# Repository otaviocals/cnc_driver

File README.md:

# Arduino Based CNC Driver
## Written by Otavio Cals

# Overview

# Installation

# Credits

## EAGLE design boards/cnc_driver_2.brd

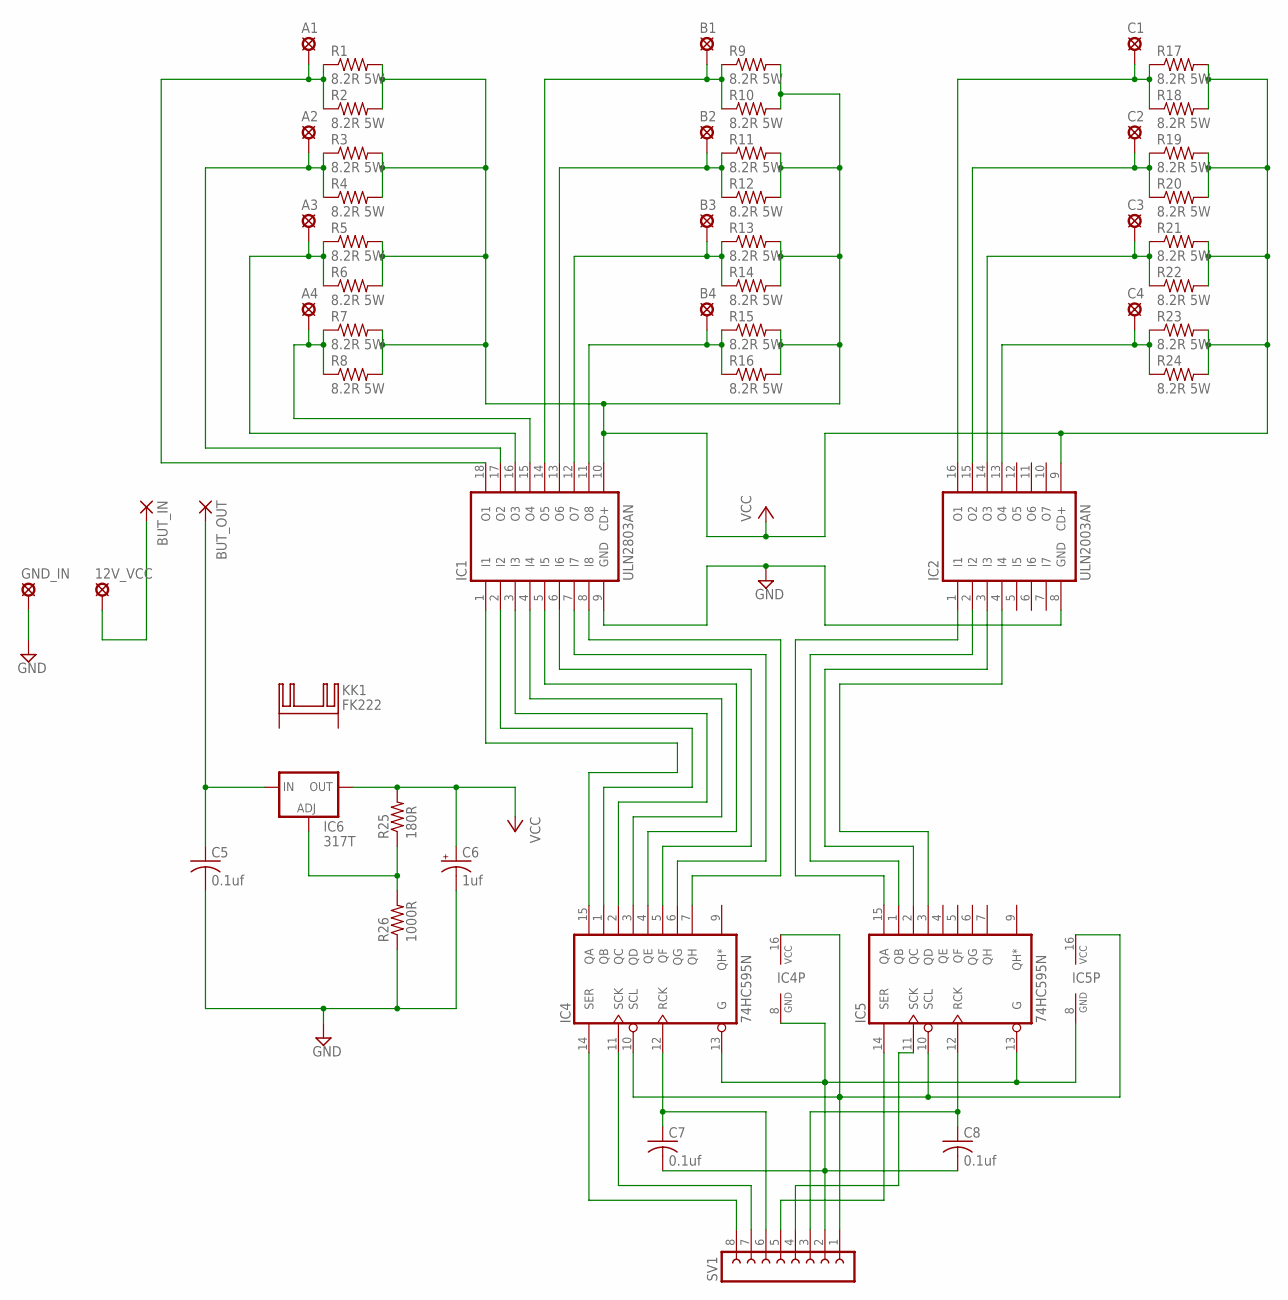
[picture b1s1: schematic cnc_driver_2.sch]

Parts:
12V_VCC: LSP13
A1, A2, A3, A4: LSP11
B1, B2, B3, B4: LSP11
BUT_IN: 3,81/1,4
BUT_OUT: 3,81/1,4
C1, C2, C3, C4: LSP11
C5, C7, C8: 0.1uf; C025-025X050
C6: 1uf; E2-5
GND_IN: LSP13
IC1: ULN2803AN; DIL18
IC2: ULN2003AN; DIL16
IC4, IC5: 74HC595N; DIL16
IC6: 317T; 317TS
KK1: FK222
R1, R2, R3, R4, R5, R6, R7, R8, R9, R10, R11, R12, R13, R14, R15, R16, R17, R18, R19, R20, R21, R22, R23, R24: 8.2R 5W; 0617V
R25: 180R; 0207/10
R26: 1000R; 0207/10
SV1: FE08-1; FE08

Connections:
GND: C5.2, C6.-, GND_IN.MP, IC1.9 (GND), IC2.8 (GND), R26.1
unnamed: A1.MP, IC1.18 (O1), R1.1, R2.1
unnamed: A2.MP, IC1.17 (O2), R3.1, R4.1
unnamed: A3.MP, IC1.16 (O3), R5.1, R6.1
unnamed: A4.MP, IC1.15 (O4), R7.1, R8.1
unnamed: 12V_VCC.MP, BUT_IN.1
unnamed: BUT_OUT.1, C5.1, IC6.3 (IN)
unnamed: IC4.10 (SCL), IC4.16 (VCC), IC5.10 (SCL), IC5.16 (VCC), SV1.1
unnamed: IC6.1 (ADJ), R25.1, R26.2
unnamed: C7.2, C8.2, IC4.8 (GND), IC4.13 (G), IC5.8 (GND), IC5.13 (G), SV1.2
unnamed: B1.MP, IC1.14 (O5), R9.1, R10.1
unnamed: B2.MP, IC1.13 (O6), R11.1, R12.1
unnamed: B3.MP, IC1.12 (O7), R13.1, R14.1
unnamed: B4.MP, IC1.11 (O8), R15.1, R16.1
unnamed: C1.MP, IC2.16 (O1), R17.1, R18.1
unnamed: C2.MP, IC2.15 (O2), R19.1, R20.1
unnamed: C3.MP, IC2.14 (O3), R21.1, R22.1
unnamed: C4.MP, IC2.13 (O4), R23.1, R24.1
unnamed: C8.1, IC5.12 (RCK), SV1.3
unnamed: C7.1, IC4.12 (RCK), SV1.6
unnamed: IC4.11 (SCK), SV1.7
unnamed: IC4.14 (SER), SV1.8
unnamed: IC1.1 (I1), IC4.15 (QA)
unnamed: IC1.2 (I2), IC4.1 (QB)
unnamed: IC1.3 (I3), IC4.2 (QC)
unnamed: IC1.4 (I4), IC4.3 (QD)
unnamed: IC1.5 (I5), IC4.4 (QE)
unnamed: IC1.6 (I6), IC4.5 (QF)
unnamed: IC1.7 (I7), IC4.6 (QG)
unnamed: IC1.8 (I8), IC4.7 (QH)
unnamed: IC2.1 (I1), IC5.15 (QA)
unnamed: IC2.2 (I2), IC5.1 (QB)
unnamed: IC2.3 (I3), IC5.2 (QC)
unnamed: IC2.4 (I4), IC5.3 (QD)
unnamed: IC5.14 (SER), SV1.5
unnamed: IC5.11 (SCK), SV1.4
VCC: IC1.10 (CD+), IC2.9 (CD+), R1.2, R2.2, R3.2, R4.2, R5.2, R6.2, R7.2, R8.2, R9.2, R10.2, R11.2, R12.2, R13.2, R14.2, R15.2, R16.2, R17.2, R18.2, R19.2, R20.2, R21.2, R22.2, R23.2, R24.2
VCC_MOTOR: C6.+, IC6.2 (OUT), R25.2

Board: 2 copper layers, 53 parts (0 on the bottom side), 38 nets, no tracks yet.

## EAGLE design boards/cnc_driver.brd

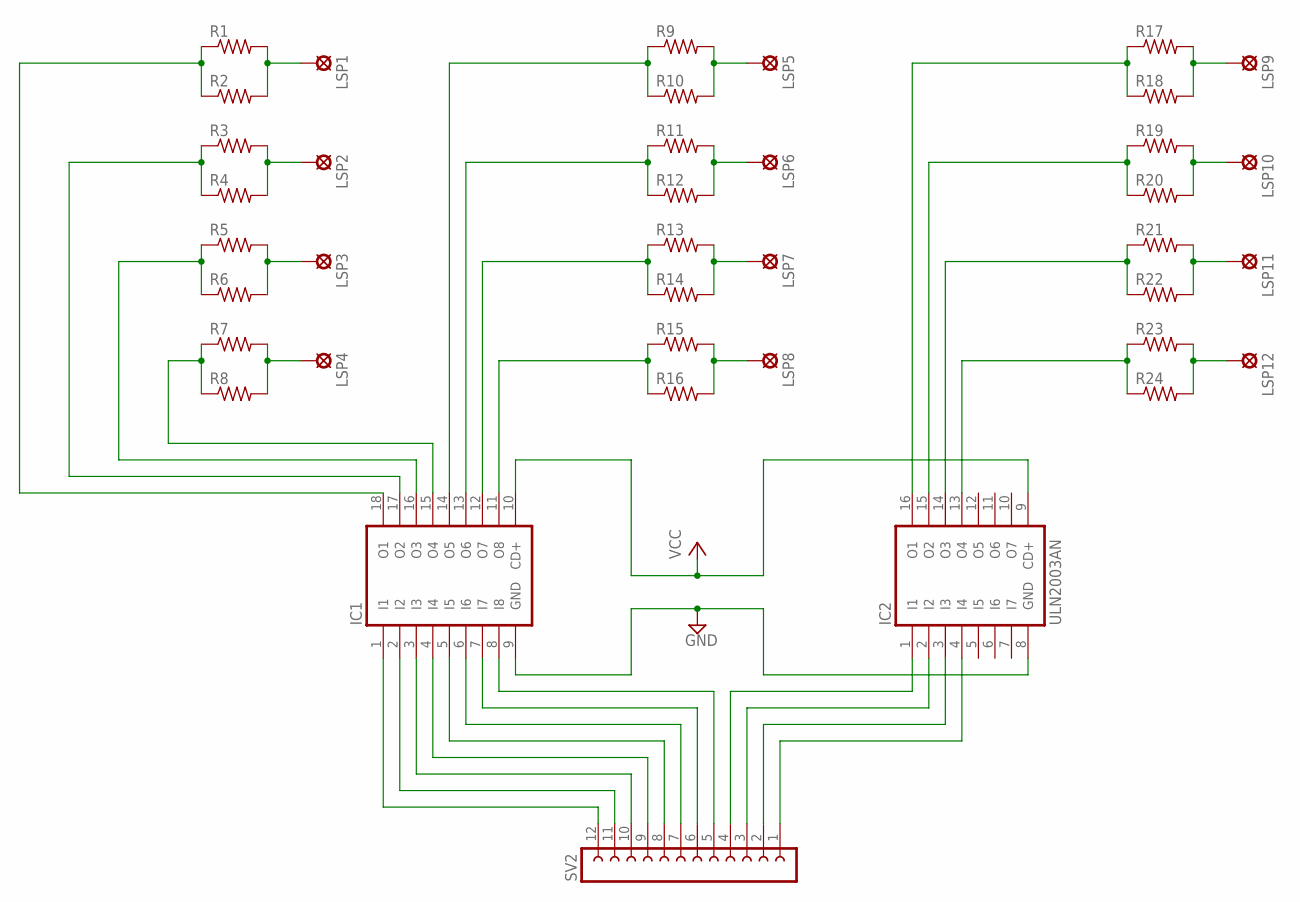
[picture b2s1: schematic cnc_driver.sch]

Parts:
IC1: ULN2803A; DIL18
IC2: ULN2003AN; DIL16
LSP1, LSP2, LSP3, LSP4, LSP5, LSP6, LSP7, LSP8, LSP9, LSP10, LSP11, LSP12: LSP11
R1, R2, R3, R4, R5, R6, R7, R8, R9, R10, R11, R12, R13, R14, R15, R16, R17, R18, R19, R20, R21, R22, R23, R24: R-US_0922V; 0922V
SV2: FE12-1; FE12

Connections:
GND: IC1.9 (GND), IC2.8 (GND)
unnamed: IC1.18 (O1), R1.1, R2.1
unnamed: IC1.17 (O2), R3.1, R4.1
unnamed: IC1.16 (O3), R5.1, R6.1
unnamed: IC1.15 (O4), R7.1, R8.1
unnamed: LSP1.MP, R1.2, R2.2
unnamed: LSP2.MP, R3.2, R4.2
unnamed: LSP3.MP, R5.2, R6.2
unnamed: LSP4.MP, R7.2, R8.2
unnamed: LSP5.MP, R9.2, R10.2
unnamed: LSP6.MP, R11.2, R12.2
unnamed: LSP7.MP, R13.2, R14.2
unnamed: LSP8.MP, R15.2, R16.2
unnamed: IC1.14 (O5), R9.1, R10.1
unnamed: IC1.13 (O6), R11.1, R12.1
unnamed: IC1.12 (O7), R13.1, R14.1
unnamed: IC1.11 (O8), R15.1, R16.1
unnamed: IC2.16 (O1), R17.1, R18.1
unnamed: IC2.15 (O2), R19.1, R20.1
unnamed: IC2.14 (O3), R21.1, R22.1
unnamed: IC2.13 (O4), R23.1, R24.1
unnamed: LSP9.MP, R17.2, R18.2
unnamed: LSP10.MP, R19.2, R20.2
unnamed: LSP11.MP, R21.2, R22.2
unnamed: LSP12.MP, R23.2, R24.2
unnamed: IC1.1 (I1), SV2.12
unnamed: IC1.2 (I2), SV2.11
unnamed: IC1.3 (I3), SV2.10
unnamed: IC1.4 (I4), SV2.9
unnamed: IC1.5 (I5), SV2.8
unnamed: IC1.6 (I6), SV2.7
unnamed: IC1.7 (I7), SV2.6
unnamed: IC1.8 (I8), SV2.5
unnamed: IC2.1 (I1), SV2.4
unnamed: IC2.2 (I2), SV2.3
unnamed: IC2.3 (I3), SV2.2
unnamed: IC2.4 (I4), SV2.1
VCC: IC1.10 (CD+), IC2.9 (CD+)

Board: 2 copper layers, 39 parts (0 on the bottom side), 38 nets, no tracks yet.

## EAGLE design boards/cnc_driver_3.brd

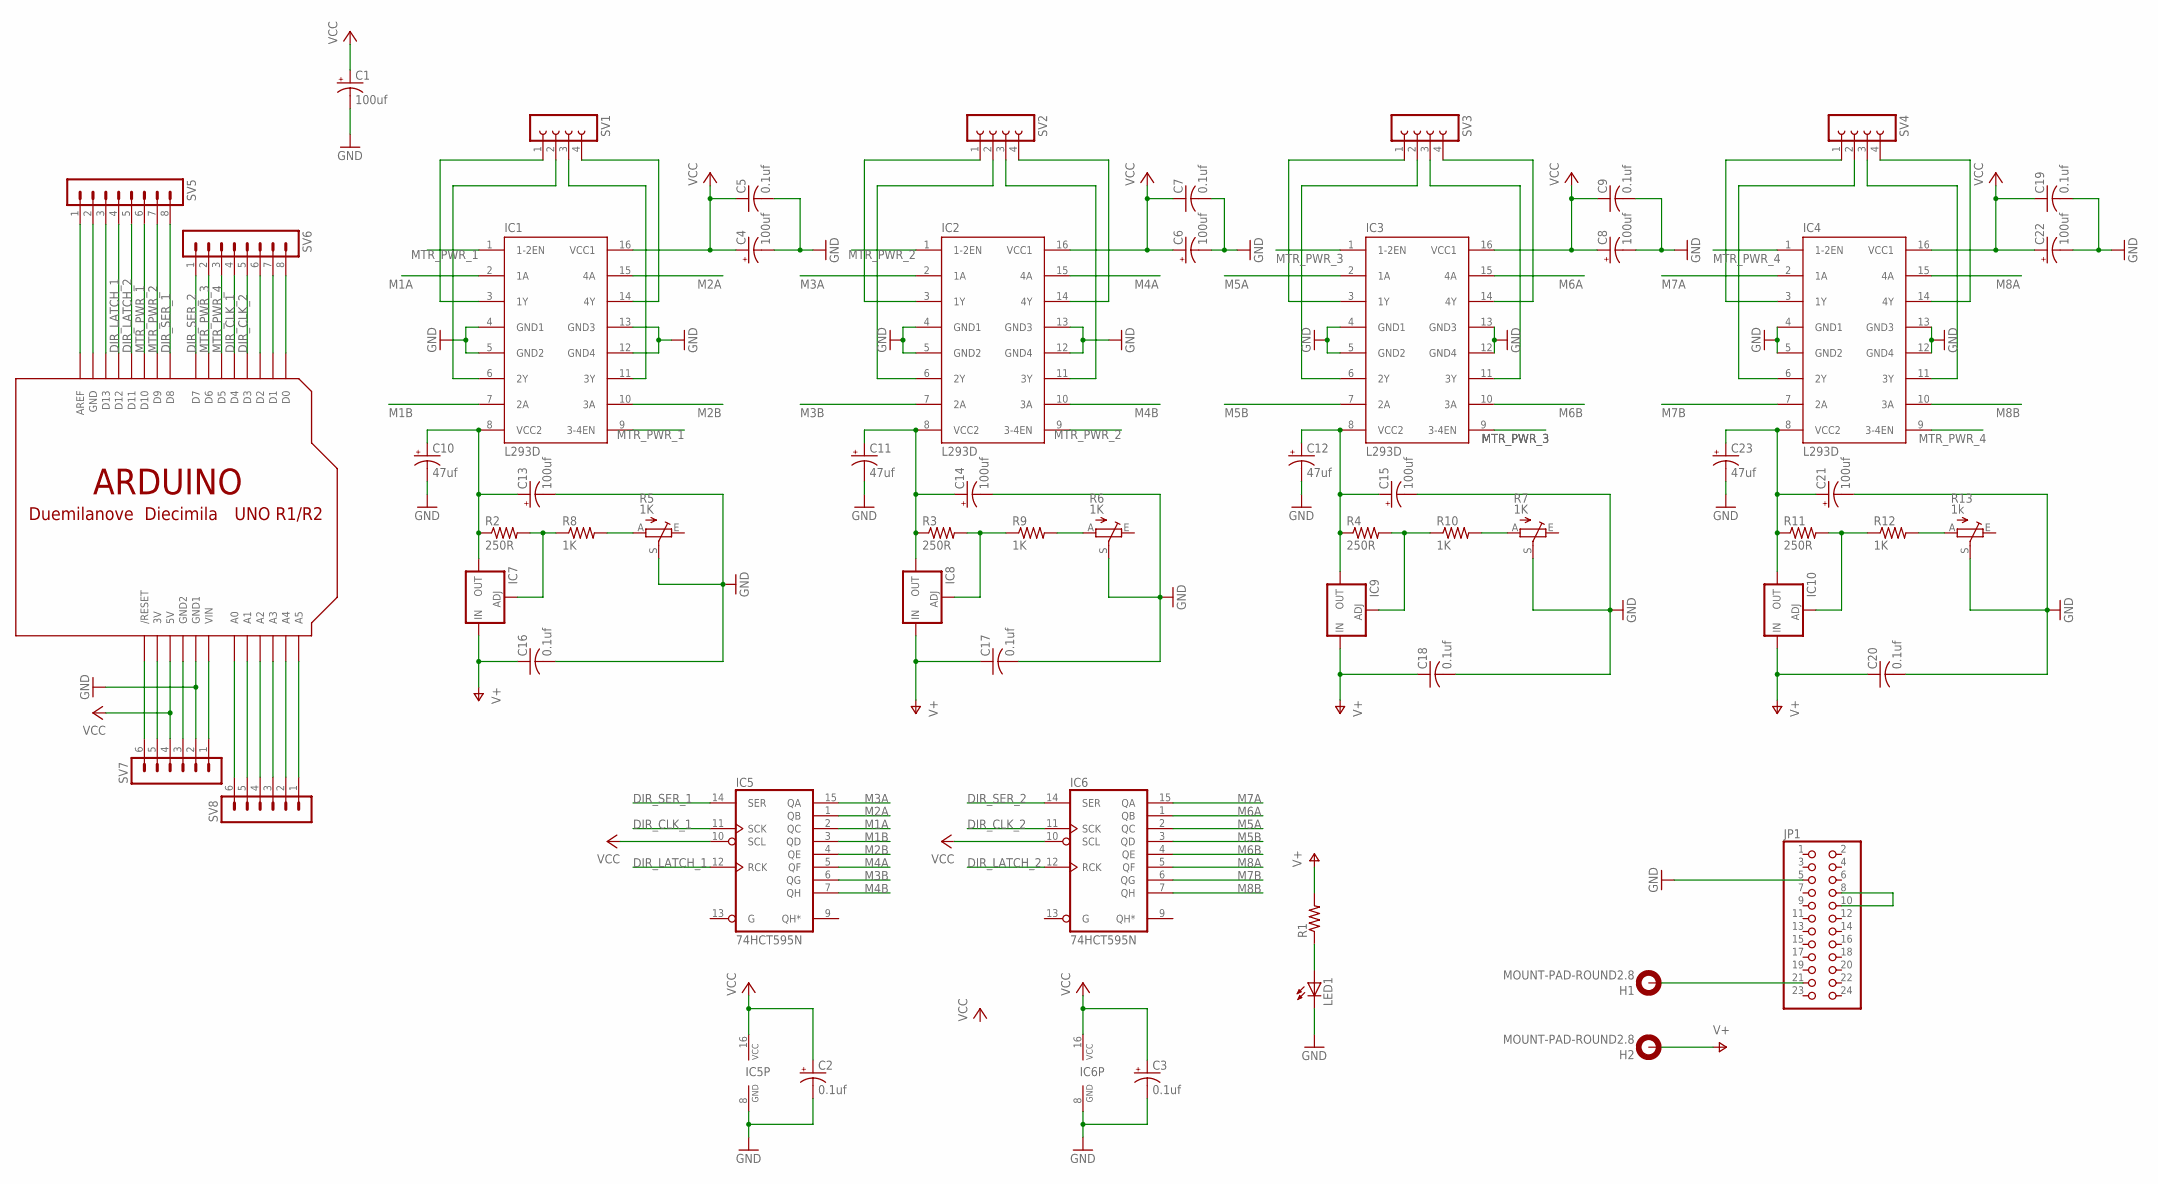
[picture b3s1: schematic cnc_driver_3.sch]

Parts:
C1, C4, C6, C8: 100uf; E2-5
C2, C3: 0.1uf; E2-5
C5, C7, C9, C19, C20: 0.1uf; C025-025X050
C10, C11, C12: 47uf; E2-5
C13, C14, C15, C21, C22: 100uf; E3,5-8
C16, C17, C18: 0.1uf; C025-024X044
C23: 47uf; E3,5-8
H1, H2: MOUNT-PAD-ROUND2.8; 2,8-PAD
IC1, IC2, IC3, IC4: L293D; DIL16
IC5, IC6: 74HCT595N; DIL16
IC7, IC8, IC9, IC10: LM317TS; 317TS
JP1: PINHD-2X12; 2X12
LED1: LED5MM
R1: R-US_0204/7; 0204/7
R2, R3, R4, R11: 250R; 0207/7
R5, R6, R7: 1K; CA9H
R8, R9, R10, R12: 1K; 0207/7
R13: 1k; CA9H
SV1, SV2, SV3, SV4: FE04-1
SV5, SV6: MA08-1
SV7, SV8: MA06-1
U$1: ARDUINOUNO; ARDUINO

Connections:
DIR_CLK_1: IC5.11 (SCK), SV6.4, U$1.D4
DIR_CLK_2: IC6.11 (SCK), SV6.5, U$1.D3
DIR_LATCH_1: IC5.12 (RCK), SV5.4, U$1.D12
DIR_LATCH_2: IC6.12 (RCK), SV5.5, U$1.D11
DIR_SER_1: IC5.14 (SER), SV5.8, U$1.D8
DIR_SER_2: IC6.14 (SER), SV6.1, U$1.D7
GND: C1.-, C2.-, C3.-, C4.-, C5.2, C6.-, C7.2, C8.-, C9.2, C10.-, C11.-, C12.-, C13.-, C14.-, C15.-, C16.2, C17.2, C18.2, C19.2, C20.2, C21.-, C22.-, C23.-, IC1.4 (GND1), IC1.5 (GND2), IC1.12 (GND4), IC1.13 (GND3), IC2.4 (GND1), IC2.5 (GND2), IC2.12 (GND4), IC2.13 (GND3), IC3.4 (GND1), IC3.5 (GND2), IC3.12 (GND4), IC3.13 (GND3), IC4.4 (GND1), IC4.5 (GND2), IC4.12 (GND4), IC4.13 (GND3), IC5.8 (GND), IC6.8 (GND), JP1.5, LED1.K (C), R5.S, R6.S, R7.S, R13.S, SV7.2, U$1.GND1
M1A: IC1.2 (1A), IC5.2 (QC)
M1B: IC1.7 (2A), IC5.3 (QD)
M2A: IC1.15 (4A), IC5.1 (QB)
M2B: IC1.10 (3A), IC5.4 (QE)
M3A: IC2.2 (1A), IC5.15 (QA)
M3B: IC2.7 (2A), IC5.6 (QG)
M4A: IC2.15 (4A), IC5.5 (QF)
M4B: IC2.10 (3A), IC5.7 (QH)
M5A: IC3.2 (1A), IC6.2 (QC)
M5B: IC3.7 (2A), IC6.3 (QD)
M6A: IC3.15 (4A), IC6.1 (QB)
M6B: IC3.10 (3A), IC6.4 (QE)
M7A: IC4.2 (1A), IC6.15 (QA)
M7B: IC4.7 (2A), IC6.6 (QG)
M8A: IC4.15 (4A), IC6.5 (QF)
M8B: IC4.10 (3A), IC6.7 (QH)
MTR_PWR_1: IC1.1 (1-2EN), IC1.9 (3-4EN), SV5.6, U$1.D10
MTR_PWR_2: IC2.1 (1-2EN), IC2.9 (3-4EN), SV5.7, U$1.D9
MTR_PWR_3: IC3.1 (1-2EN), IC3.9 (3-4EN), SV6.2, U$1.D6
MTR_PWR_4: IC4.1 (1-2EN), IC4.9 (3-4EN), SV6.3, U$1.D5
unnamed: IC1.3 (1Y), SV1.1
unnamed: IC1.6 (2Y), SV1.2
unnamed: IC1.11 (3Y), SV1.3
unnamed: IC1.14 (4Y), SV1.4
unnamed: LED1.A, R1.1
unnamed: R6.A, R9.2
unnamed: C10.+, C13.+, IC1.8 (VCC2), IC7.2 (OUT), R2.1
unnamed: IC2.3 (1Y), SV2.1
unnamed: IC2.6 (2Y), SV2.2
unnamed: IC2.11 (3Y), SV2.3
unnamed: IC2.14 (4Y), SV2.4
unnamed: IC3.3 (1Y), SV3.1
unnamed: IC3.6 (2Y), SV3.2
unnamed: IC3.14 (4Y), SV3.4
unnamed: IC3.11 (3Y), SV3.3
unnamed: IC7.1 (ADJ), R2.2, R8.1
unnamed: R5.A, R8.2
unnamed: IC8.1 (ADJ), R3.2, R9.1
unnamed: C11.+, C14.+, IC2.8 (VCC2), IC8.2 (OUT), R3.1
unnamed: IC9.1 (ADJ), R4.2, R10.1
unnamed: C12.+, C15.+, IC3.8 (VCC2), IC9.2 (OUT), R4.1
unnamed: R7.A, R10.2
unnamed: C21.+, C23.+, IC4.8 (VCC2), IC10.2 (OUT), R11.1
unnamed: IC10.1 (ADJ), R11.2, R12.1
unnamed: R12.2, R13.A
unnamed: IC4.11 (3Y), SV4.3
unnamed: IC4.6 (2Y), SV4.2
unnamed: IC4.3 (1Y), SV4.1
unnamed: IC4.14 (4Y), SV4.4
unnamed: JP1.8, JP1.10
unnamed: H1.B2,8, JP1.21
unnamed: SV7.6, U$1.RESET (/RESET)
unnamed: SV5.1, U$1.AREF
unnamed: SV5.2, U$1.GND
unnamed: SV5.3, U$1.D13
unnamed: SV6.6, U$1.D2
unnamed: SV6.7, U$1.D1
unnamed: SV6.8, U$1.D0
unnamed: SV7.5, U$1.3V
unnamed: SV7.3, U$1.GND2
unnamed: SV7.1, U$1.VIN
unnamed: SV8.6, U$1.A0
unnamed: SV8.5, U$1.A1
unnamed: SV8.4, U$1.A2
unnamed: SV8.3, U$1.A3
unnamed: SV8.2, U$1.A4
unnamed: SV8.1, U$1.A5
V+: C16.1, C17.1, C18.1, C20.1, H2.B2,8, IC7.3 (IN), IC8.3 (IN), IC9.3 (IN), IC10.3 (IN), R1.2
VCC: C1.+, C2.+, C3.+, C4.+, C5.1, C6.+, C7.1, C8.+, C9.1, C19.1, C22.+, IC1.16 (VCC1), IC2.16 (VCC1), IC3.16 (VCC1), IC4.16 (VCC1), IC5.10 (SCL), IC5.16 (VCC), IC6.10 (SCL), IC6.16 (VCC), SV7.4, U$1.5V

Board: 2 copper layers, 63 parts (3 on the bottom side), 76 nets, no tracks yet.

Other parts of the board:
U$2, U$3, U$4, U$5: FK213

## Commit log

2017-05-11 first sketch
2017-05-11 changed readme
2017-05-11 added stepper 2 buttons
2017-05-11 added serial test
2017-05-12 changes to driver
2017-05-17 added boards schematics
2017-05-19 added new versions
